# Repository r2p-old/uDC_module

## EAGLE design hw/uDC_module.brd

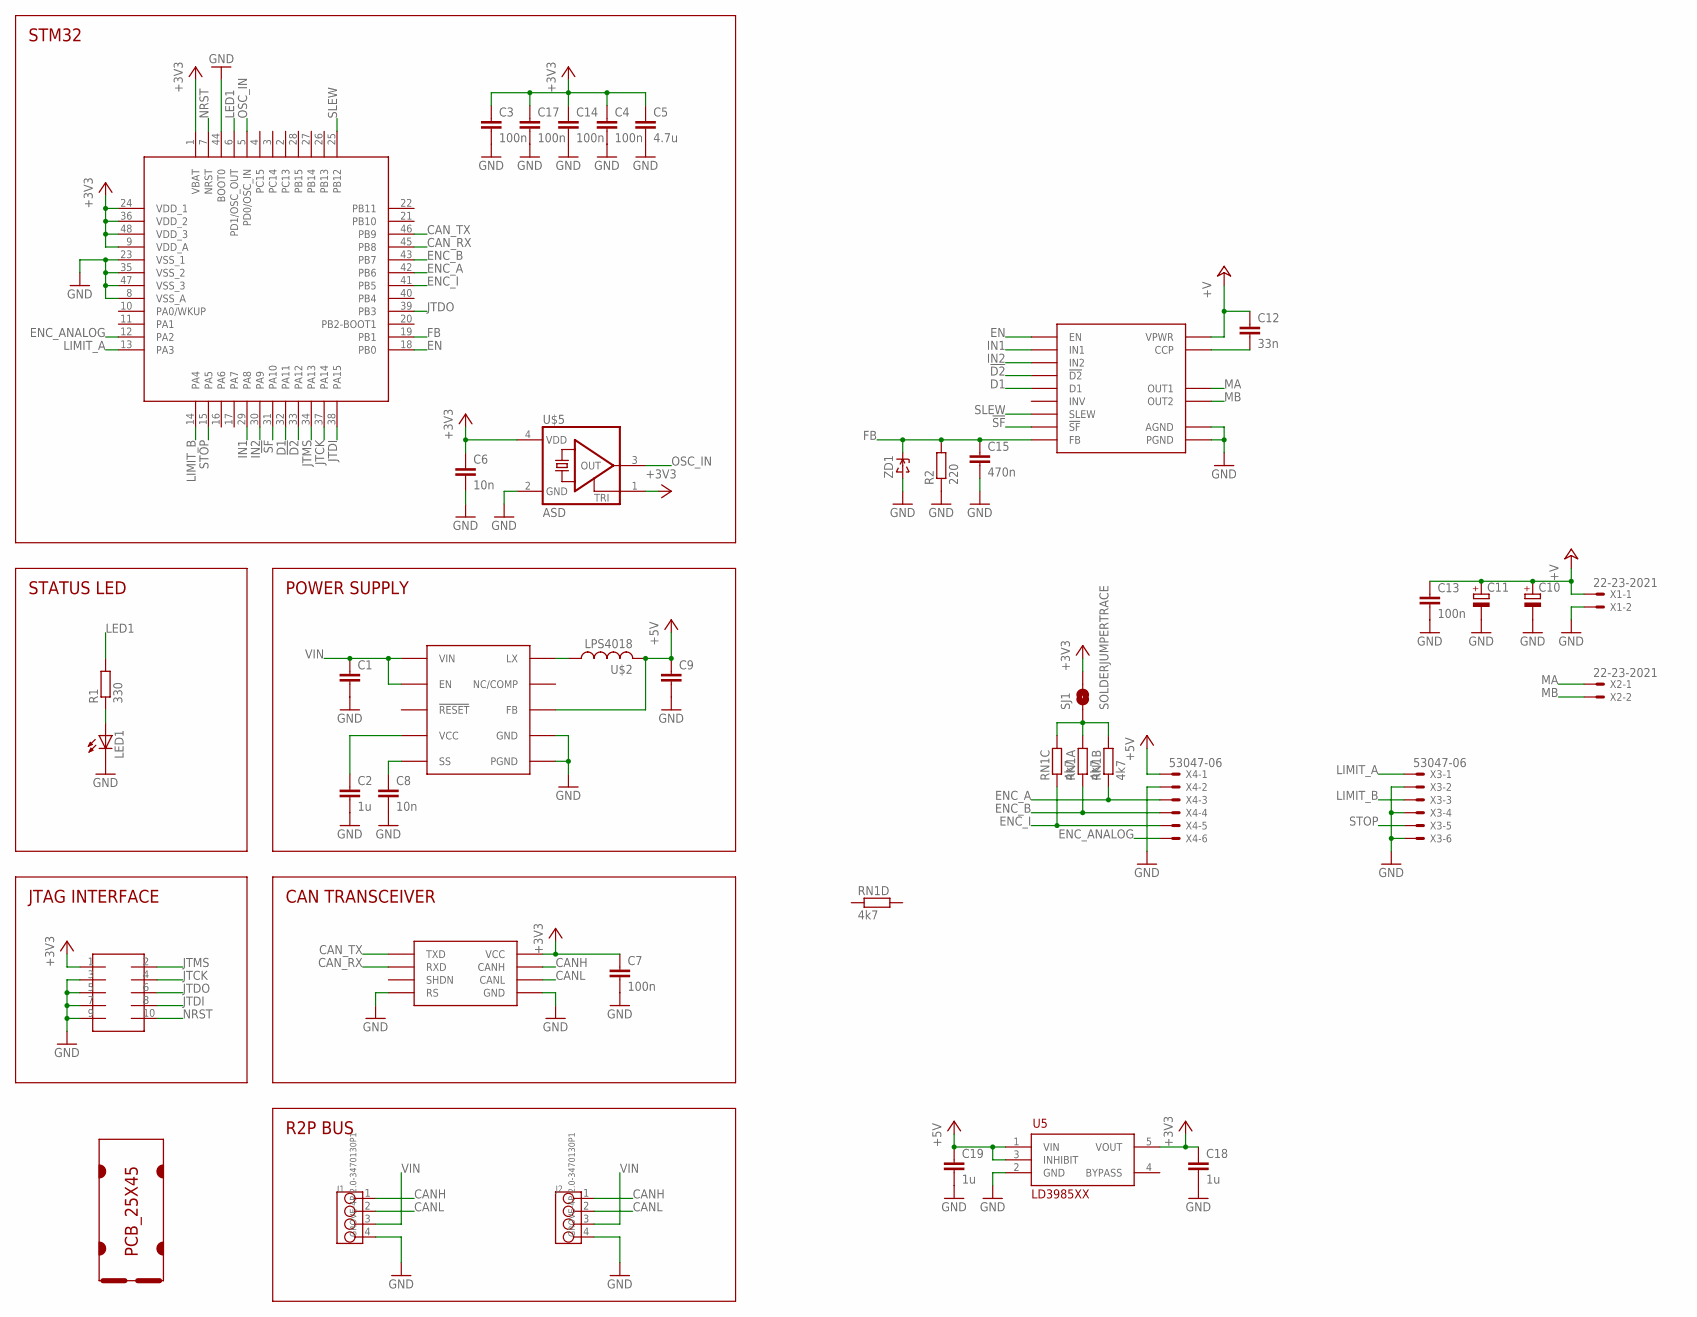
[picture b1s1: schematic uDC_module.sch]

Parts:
C1: C-EUC1206; C1206
C2, C18, C19: 1u; C0603
C3, C4, C7, C13, C14, C17: 100n; C0603
C5: 4.7u; C0805
C6, C8: 10n; C0603
C9: C-EUC0805; C0805
C10, C11: CPOL-EUD; PANASONIC_D
C12: 33n; C0603
C15: 470n; C0603
J1, J2: GROVE-4P-2.0-3470130P1; 4P-2.0
LED1: LEDCHIPLED_0805; CHIPLED_0805
R1: 330; R0603
R2: 220; R0603
RN1: 4k7; RN8P-4R-CRA06S
SJ1: SOLDERJUMPERTRACE; SJ_2S-TRACE
SOT1: MAX3051EKA; SOT23-8L
U5: LD3985XX; SOT23-5L
U$1: PCB_25X45; 25X45
U$2: LPS4018
U$3: MAX17501; TDFN-10
U$4: FTSH-105TH; FTSH-105-TH
U$5: ASD; 2.5X2
U$6: STM32F103CXTX; LQFP48
U$7: MC33962; PQFN32
X1, X2: 22-23-2021
X3, X4: 53047-06
ZD1: ZENERSOD-323F; SOD-323F

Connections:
!D2: U$6.33 (PA12), U$7.P$16 (!D2)
!SF: U$6.31 (PA10), U$7.P$21 (!SF)
+3V3: C3.1, C4.1, C5.1, C6.1, C7.1, C14.1, C17.1, C18.1, SJ1.2, SOT1.3 (VCC), U5.5 (VOUT), U$4.1, U$5.1 (TRI), U$5.4 (VDD), U$6.1 (VBAT), U$6.9 (VDD_A), U$6.24 (VDD_1), U$6.36 (VDD_2), U$6.48 (VDD_3)
+5V: C9.1, C19.1, U5.1 (VIN), U5.3 (INHIBIT), U$2.P$2 (2), U$3.P$5 (FB), X4.1
+V: C10.+, C11.+, C12.1, C13.1, U$7.P$4 (VPWR), U$7.P$6 (VPWR), U$7.P$11 (VPWR), U$7.P$31 (VPWR), X1.1
CANH: J1.1, J2.1, SOT1.7 (CANH)
CANL: J1.2, J2.2, SOT1.6 (CANL)
CAN_RX: SOT1.4 (RXD), U$6.45 (PB8)
CAN_TX: SOT1.1 (TXD), U$6.46 (PB9)
D1: U$6.32 (PA11), U$7.P$26 (D1)
EN: U$6.18 (PB0), U$7.P$10 (EN)
ENC_A: RN1.2 (1), U$6.42 (PB6), X4.3
ENC_ANALOG: U$6.12 (PA2), X4.6
ENC_B: RN1.1, U$6.43 (PB7), X4.4
ENC_I: RN1.3 (1), U$6.41 (PB5), X4.5
FB: C15.1, R2.2, U$6.19 (PB1), U$7.P$8 (FB), ZD1.C
GND: C1.2, C2.2, C3.2, C4.2, C5.2, C6.2, C7.2, C8.2, C9.2, C10.-, C11.-, C13.2, C14.2, C15.2, C17.2, C18.2, C19.2, J1.4, J2.4, LED1.C, R2.1, SOT1.2 (GND), SOT1.8 (RS), U5.2 (GND), U$3.P$1 (PGND), U$3.P$9 (GND), U$3.P$11 (PGND), U$4.3, U$4.5, U$4.7, U$4.9, U$5.2 (GND), U$6.8 (VSS_A), U$6.23 (VSS_1), U$6.35 (VSS_2), U$6.44 (BOOT0), U$6.47 (VSS_3), U$7.P$5 (AGND), U$7.P$18 (PGND), U$7.P$19 (PGND), U$7.P$20 (PGND), U$7.P$22 (PGND), U$7.P$23 (PGND), U$7.P$24 (PGND), U$7.P$33 (AGND), X1.2, X3.2, X3.4, X3.6, X4.2, ZD1.A
IN1: U$6.29 (PA8), U$7.P$2 (IN1)
IN2: U$6.30 (PA9), U$7.P$1 (IN2)
JTCK: U$4.4, U$6.37 (PA14)
JTDI: U$4.8, U$6.38 (PA15)
JTDO: U$4.6, U$6.39 (PB3)
JTMS: U$4.2, U$6.34 (PA13)
LED1: R1.2, U$6.6 (PD1/OSC_OUT)
LIMIT_A: U$6.13 (PA3), X3.1
LIMIT_B: U$6.14 (PA4), X3.3
MA: U$7.P$12 (OUT1), U$7.P$13 (OUT1), U$7.P$14 (OUT1), U$7.P$15 (OUT1), X2.1
MB: U$7.P$27 (OUT2), U$7.P$28 (OUT2), U$7.P$29 (OUT2), U$7.P$30 (OUT2), X2.2
unnamed: U$2.P$1 (1), U$3.P$10 (LX)
unnamed: LED1.A, R1.1
unnamed: RN1.6 (2), RN1.7 (2), RN1.8 (2), SJ1.1
unnamed: C12.2, U$7.P$32 (CCP)
unnamed: C2.1, U$3.P$4 (VCC)
unnamed: C8.1, U$3.P$6 (SS)
NRST: U$4.10, U$6.7 (NRST)
OSC_IN: U$5.3 (OUT), U$6.5 (PD0/OSC_IN)
SLEW: U$6.25 (PB12), U$7.P$3 (SLEW)
STOP: U$6.15 (PA5), X3.5
VIN: C1.1, J1.3, J2.3, U$3.P$2 (VIN), U$3.P$3 (EN)

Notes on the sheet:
STM32
STATUS LED
JTAG INTERFACE
POWER SUPPLY
CAN TRANSCEIVER
R2P BUS

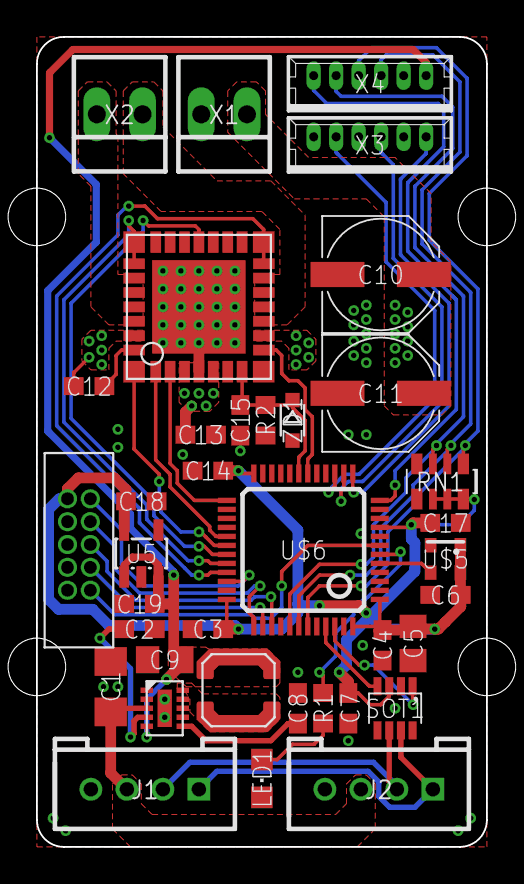
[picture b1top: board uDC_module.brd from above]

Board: 2 copper layers, 25.0 x 45.0 mm, 39 parts (1 on the bottom side), 39 nets.

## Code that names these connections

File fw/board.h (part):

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#define GPIOF_PIN14                 14
#define GPIOF_PIN15                 15

#define LED1_GPIO	GPIOC
#define LED2_GPIO	GPIOC
#define LED3_GPIO	GPIOC
#define LED4_GPIO	GPIOC
#define LED1		13
#define LED2		13
#define LED3		13
#define LED4		13
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 *
 * PA0  - PIN0                      (input pullup).
 * PA1  - PIN1                      (input pullup).
 * PA2  - ENCODER_ANALOG            (analog).
 * PA3  - SWITCH_A                  (input pullup).
 * PA4  - SWITCH_B                  (input pullup).
 * PA5  - SWITCH_STOP               (input pullup).
 * PA6  - PIN6                      (input pullup).
 * PA7  - PIN7                      (input pullup).
 * PA8  - MOTOR_IN1                 (alternate 6).
 * PA9  - MOTOR_IN2                 (alternate 6).
 * PA10 - MOTOR_SF                  (input pullup).
 * PA11 - MOTOR_D1                  (output pushpull maximum).
 * PA12 - MOTOR_D2                  (output pushpull maximum).
 * PA13 - JTAG_TMS                  (alternate 0).
 * PA14 - JTAG_TCK                  (alternate 0).
 * PA15 - JTAG_TDI                  (alternate 0).
 */
#define VAL_GPIOA_MODER             (PIN_MODE_INPUT(GPIOA_PIN0) |           \
                                     PIN_MODE_INPUT(GPIOA_PIN1) |           \
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/*
 * GPIOB setup:
 *
 * PB0  - MOTOR_ENABLE              (output pushpull maximum).
 * PB1  - MOTOR_FEEDBACK            (analog).
 * PB2  - BOOT1                     (input floating).
 * PB3  - JTAG_TDO                  (alternate 0).
 * PB4  - JTAG_TRST                 (alternate 0).
 * PB5  - ENCODER_I                 (input pullup).
 * PB6  - ENCODER_A                 (alternate 2).
 * PB7  - ENCODER_B                 (alternate 2).
 * PB8  - CAN_RX                    (alternate 9).
 * PB9  - CAN_TX                    (alternate 9).
 * PB10 - PIN10                     (input pullup).
 * PB11 - PIN11                     (input pullup).
 * PB12 - MOTOR_SLEW                (output pushpull maximum).
 * PB13 - PIN13                     (input pullup).
 * PB14 - PIN14                     (input pullup).
 * PB15 - PIN15                     (input pullup).
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/*
 * GPIOD setup:
 *
 * PD0  - PIN0                      (input pullup).
 * PD1  - PIN1                      (input pullup).
 * PD2  - PIN2                      (input pullup).
 * PD3  - PIN3                      (input pullup).
 * PD4  - PIN4                      (input pullup).
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
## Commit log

2014-05-29 added motor driver datasheet
2014-05-29 ongoing layout
2014-05-30 hi-power section layout completed
2014-05-30 working on signal routing
2014-05-30 working on signal routin
2014-06-03 routing encoder signals
2014-06-03 layout completed
2014-06-04 updated all connectors to have GND on pin 1
2014-06-13 final revision
2014-06-23 Added makefile for quicker gerber generation
2014-06-24 added PNG of board layout
2014-07-31 added blinking led firmware
2014-08-08 moved IN2 to TIM1 ch2
2014-08-08 updated config to STM32F3 and added hardware_test firmware
2014-12-16 small fixes for production
2014-12-16 small fixes
2014-12-29 approved DRC false errors
2015-01-08 added logo to bottom silkscreen
2015-01-09 updated paths
2015-01-13 minor fixes for manufacturing
2015-01-22 added assembly PDF generation

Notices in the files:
fw/board.h:
ChibiOS/RT - Copyright (C) 2006-2013 Giovanni Di Sirio
Licensed under the Apache License, Version 2.0 (the "License");
parts and their libraries:
SparkFun: Licensing: CC v3.0 Share-Alike You are welcome to use this library for commercial purposes.
